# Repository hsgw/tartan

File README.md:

Tartan
================================

60% keyboard made by through hole components only. 

Atmega328p with VUSB on [QMK firmware](https://github.com/qmk/qmk_firmware).

[Build guide and bom is here](./doc)
[ビルドガイドとパーツリストはこちら](./doc)

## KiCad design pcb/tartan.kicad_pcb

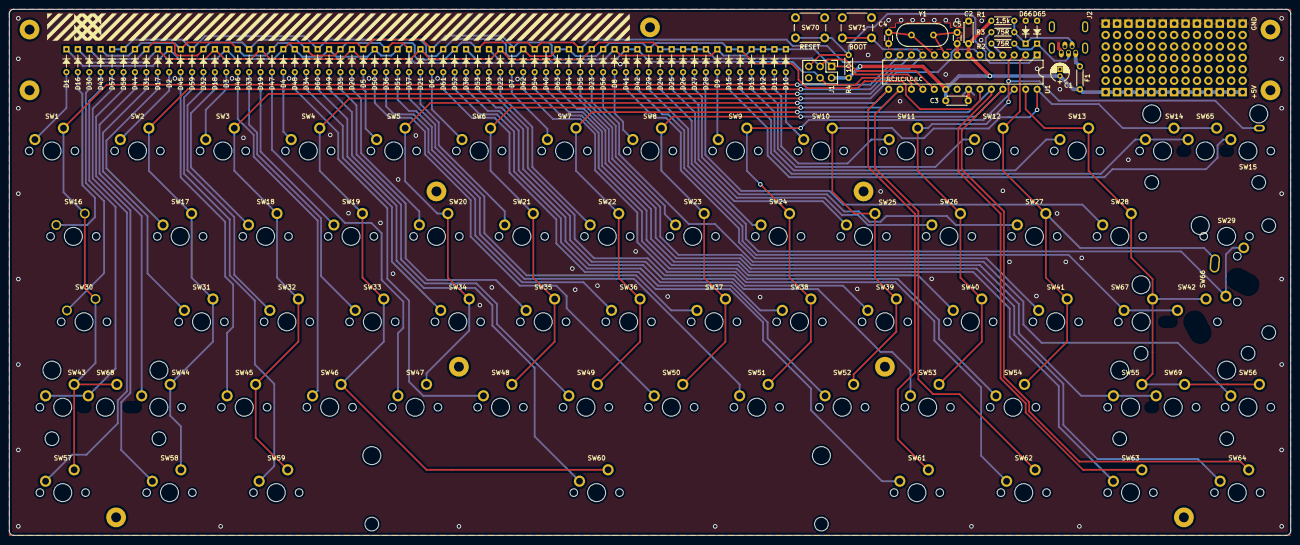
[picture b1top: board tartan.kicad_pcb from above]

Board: 2 copper layers, 285.0 x 117.0 mm, 169 parts (0 on the bottom side), 92 nets.

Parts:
C1: 10u; CP_Radial_D4.0mm_P1.50mm
C2, C3: 100n; C_Disc_D4.3mm_W1.9mm_P5.00mm
C4, C5: 20p; C_Disc_D3.0mm_W1.6mm_P2.50mm
D1, D2, D3, D4, D5, D6, D7, D8, D9, D10, D11, D12, D13, D14, D15, D16, D17, D18, D19, D20, D21, D22, D23, D24, D25, D26, D27, D28, D29, D30, D31, D32, D33, D34, D35, D36, D37, D38, D39, D40, D41, D42, D43, D44, D45, D46, D47, D48, D49, D50, D51, D52, D53, D54, D55, D56, D57, D58, D59, D60, D61, D62, D63, D64: 1N4148; D_DO-35_SOD27_P5.08mm_Horizontal
D65, D66: 3.6V; D_DO-35_SOD27_P5.08mm_Horizontal
F1: 100mA; polyfuse_5.1mm
H1, H2, H3, H4, H5, H6, H7, H8, H9, H10, H11: M2; MountingHole_2.2mm_M2_Pad
J1: AVR_ISP_6; Pin_Header_Straight_2x03_Pitch2.54mm
J2: USB_OTG; USB_MINIB_Akizuki_MUSB-5BF01AS
R1: 1.5k; R_Axial_DIN0204_L3.6mm_D1.6mm_P5.08mm_Horizontal
R2, R3: 75R; R_Axial_DIN0204_L3.6mm_D1.6mm_P5.08mm_Horizontal
R4: 10k; R_Axial_DIN0204_L3.6mm_D1.6mm_P5.08mm_Horizontal
STAB1, STAB2, STAB3, STAB4, STAB5: 2U; Stab_MX_2u
STAB6: 2U; SW_Cherry_MX1A_6.25u_PCB
SW1, SW2, SW3, SW4, SW5, SW6, SW7, SW8, SW9, SW10, SW11, SW12, SW13, SW14, SW15, SW17, SW18, SW19, SW20, SW21, SW22, SW23, SW24, SW25, SW26, SW27, SW28, SW31, SW32, SW33, SW34, SW35, SW36, SW37, SW38, SW39, SW40, SW41, SW42, SW43, SW44, SW45, SW46, SW47, SW48, SW49, SW50, SW51, SW52, SW53, SW54, SW56, SW60, SW65, SW67, SW68, SW69: SW_Push; SW_Cherry_MX1A_1.00u_PCB
SW16, SW29, SW66: SW_Push; SW_Cherry_MX1A_1.50u_PCB
SW30, SW55: SW_Push; SW_Cherry_MX1A_1.75u_PCB
SW57, SW58, SW59, SW61, SW62, SW63, SW64: SW_Push; SW_Cherry_MX1A_1.25u_PCB
SW70: RESET; SW_PUSH_6mm
SW71: BOOT; SW_PUSH_6mm
TH1: universal area; universal_area
U1: ATMEGA328-PU; DIP-28_W7.62mm
Y1: 16MHz; Crystal_HC49-4H_Vertical

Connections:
+5V: C1.1, C2.1, C3.1, F1.2, J1.2, R1.2, R4.1, TH1.1, U1.7, U1.20
/COL0: SW1.2, SW16.2, SW30.2, SW43.2, SW57.2, SW68.2, U1.13
/COL1: SW2.2, SW17.2, SW31.2, SW44.2, SW58.2, U1.12
/COL2: SW3.2, SW18.2, SW32.2, SW45.2, SW59.2, SW71.1, U1.11
/COL3: SW4.2, SW19.2, SW33.2, SW46.2, SW60.2, U1.6
/COL4: SW5.2, SW20.2, SW34.2, SW47.2, SW61.2, U1.15
/COL5: SW6.2, SW21.2, SW35.2, SW48.2, SW62.2, U1.16
/COL6: SW7.2, SW22.2, SW36.2, SW49.2, SW63.2, U1.24
/COL7: SW8.2, SW23.2, SW37.2, SW50.2, SW64.2, U1.25
/COL8: SW9.2, SW24.2, SW38.2, SW51.2, U1.26
/COL9: SW10.2, SW14.2, SW25.2, SW39.2, SW52.2, SW65.2, U1.28
/COL10: SW11.2, SW15.2, SW26.2, SW40.2, SW53.2, U1.3
/COL11: SW12.2, SW27.2, SW29.2, SW41.2, SW54.2, U1.2
/COL12: SW13.2, SW28.2, SW42.2, SW55.2, SW56.2, SW67.2, SW69.2, U1.27
/RESET: J1.5, R4.2, SW70.1, U1.1
/ROW0: D1.1, D2.1, D3.1, D4.1, D5.1, D6.1, D7.1, D8.1, D9.1, D10.1, D11.1, D12.1, D13.1, J1.1, U1.18
/ROW1: D16.1, D17.1, D18.1, D19.1, D20.1, D21.1, D22.1, D23.1, D24.1, D25.1, D26.1, D27.1, D28.1, J1.3, U1.19
/ROW2: D30.1, D31.1, D32.1, D33.1, D34.1, D35.1, D36.1, D37.1, D38.1, D39.1, D40.1, D41.1, D42.1, J1.4, U1.17
/ROW3: D43.1, D44.1, D45.1, D46.1, D47.1, D48.1, D49.1, D50.1, D51.1, D52.1, D53.1, D54.1, D55.1, U1.14
/ROW4: D14.1, D15.1, D29.1, D56.1, D57.1, D58.1, D59.1, D60.1, D61.1, D62.1, D63.1, D64.1, U1.23
/USB_D+: R2.1, U1.4
/USB_D-: R3.1, U1.5
GND: C1.2, C2.2, C3.2, C4.2, C5.2, D65.2, D66.2, J1.6, J2.5, SW70.2, SW71.2, TH1.2, U1.8, U1.22
unnamed: C4.1, U1.10, Y1.2
unnamed: C5.1, U1.9, Y1.1
unnamed: D1.2, SW1.1
unnamed: D2.2, SW2.1
unnamed: D3.2, SW3.1
unnamed: D4.2, SW4.1
unnamed: D5.2, SW5.1
unnamed: D6.2, SW6.1
unnamed: D7.2, SW7.1
unnamed: D8.2, SW8.1
unnamed: D9.2, SW9.1
unnamed: D10.2, SW10.1
unnamed: D11.2, SW11.1
unnamed: D12.2, SW12.1
unnamed: D13.2, SW13.1
unnamed: D14.2, SW14.1, SW65.1
unnamed: D15.2, SW15.1
unnamed: D16.2, SW16.1
unnamed: D17.2, SW17.1
unnamed: D18.2, SW18.1
unnamed: D19.2, SW19.1
unnamed: D20.2, SW20.1
unnamed: D21.2, SW21.1
unnamed: D22.2, SW22.1
unnamed: D23.2, SW23.1
unnamed: D24.2, SW24.1
unnamed: D25.2, SW25.1
unnamed: D26.2, SW26.1
unnamed: D27.2, SW27.1
unnamed: D28.2, SW28.1
unnamed: D29.2, SW29.1, SW66.1
unnamed: D30.2, SW30.1
unnamed: D31.2, SW31.1
unnamed: D32.2, SW32.1
unnamed: D33.2, SW33.1
unnamed: D34.2, SW34.1
unnamed: D35.2, SW35.1
unnamed: D36.2, SW36.1
unnamed: D37.2, SW37.1
unnamed: D38.2, SW38.1
unnamed: D39.2, SW39.1
unnamed: D40.2, SW40.1
unnamed: D41.2, SW41.1
unnamed: D42.2, SW42.1, SW67.1
unnamed: D43.2, SW43.1, SW68.1
unnamed: D44.2, SW44.1
unnamed: D45.2, SW45.1
unnamed: D46.2, SW46.1
unnamed: D47.2, SW47.1
unnamed: D48.2, SW48.1
unnamed: D49.2, SW49.1
unnamed: D50.2, SW50.1
unnamed: D51.2, SW51.1
unnamed: D52.2, SW52.1
unnamed: D53.2, SW53.1
unnamed: D54.2, SW54.1
unnamed: D55.2, SW55.1, SW69.1
unnamed: D56.2, SW56.1
unnamed: D57.2, SW57.1
unnamed: D58.2, SW58.1
unnamed: D59.2, SW59.1
unnamed: D60.2, SW60.1
unnamed: D61.2, SW61.1
unnamed: D62.2, SW62.1
unnamed: D63.2, SW63.1
unnamed: D64.2, SW64.1
unnamed: D65.1, J2.3, R2.2
unnamed: D66.1, J2.2, R1.1, R3.2
unnamed: F1.1, J2.1

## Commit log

2019-05-14 alpha
2019-05-21 fix alpha issues
2019-07-23 rev.Alpha2
2019-07-28 add document
2019-08-05 Update BOM.md
    fix value
2019-09-06 update doc
2019-09-06 update doc
    fix typo, add image
2020-01-16 update flash command
2020-01-30 update document
2020-12-05 add missing img

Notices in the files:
pcb/tartan.kicad_pcb:
(c)2019 Takuya Urakawa, Dm9Records, 5z6p.com
